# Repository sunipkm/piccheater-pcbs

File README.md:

# PICTURE-C/D Heater Controller PCBs
- `dac-brd`: Raspberry Pi Pico 2 based board with 2x 8 channel DACs supplied by a 2.048V precision reference voltage.
- `amp-mezzanine-v2`: A mezzanine board that supports stacking 4x AMP boards. The mezzanine takes power and control signals and pass them to the AMP boards.
- `amp-brd-v3`: A DC-DC converter board with controllable reference voltage that allows adjusting its output voltage between 0V (1V control) and 25.7V (0V control, V<sub>in</sub> > 25.7V). An on-board INA233 monitors the output voltage and current, and a DS28EA00 1-Wire temperature sensor reports board temperature.
- `amp-brd-v4`: A future, in-development version that integrates monitoring and control features using a USB-PD chip. It would allow all 16 boards on one stack.

This repository is a submodule of [`piccheater`](https://github.com/sunipkm/piccheater).

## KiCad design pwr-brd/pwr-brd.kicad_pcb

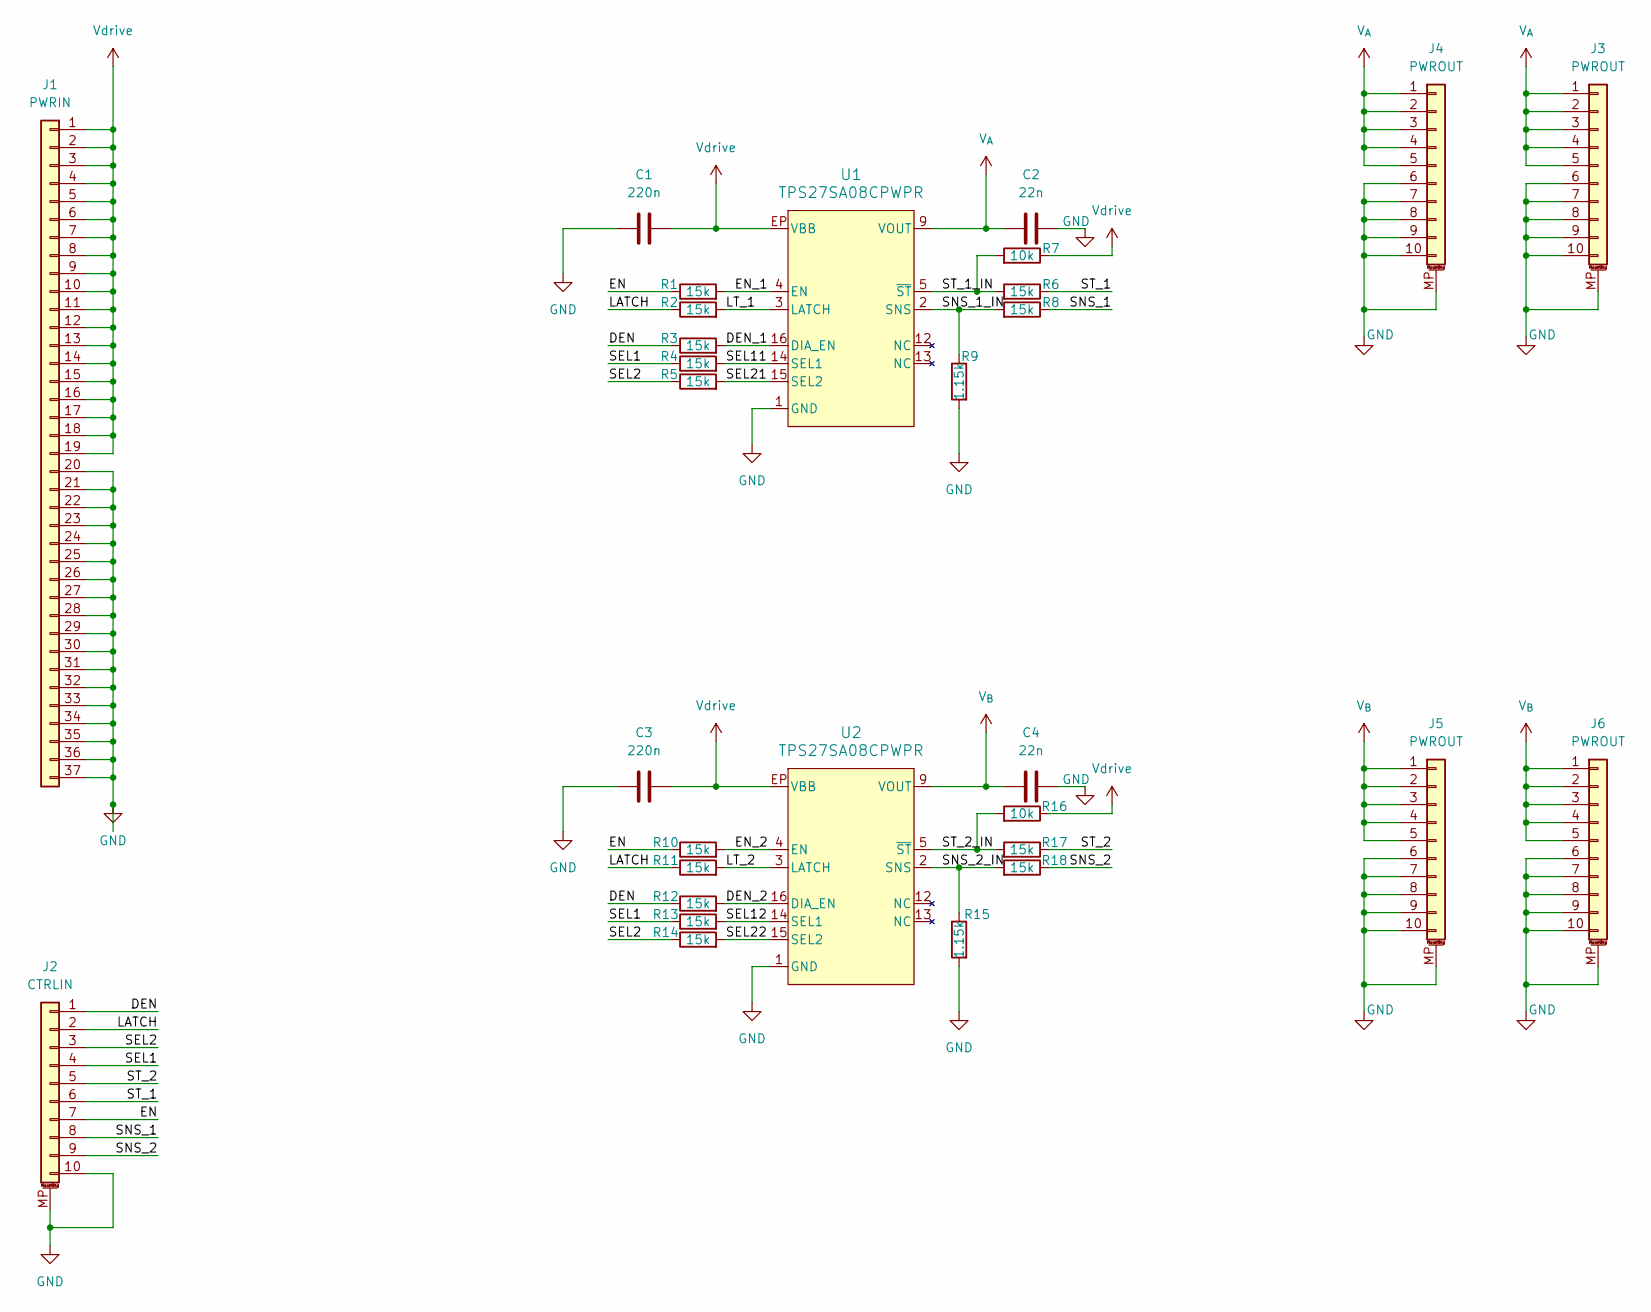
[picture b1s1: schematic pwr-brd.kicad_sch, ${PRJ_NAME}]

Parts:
C1, C3: 220n; C_0603_1608Metric; Mfr # CGA3E3X7R1H224K080AE
C2, C4: 22n; C_0603_1608Metric; Mfr # CGA3E2X8R1H223K080AE
J1: PWRIN; CONN_D37P33E4GX00LF_AMP
J2: CTRLIN; Molex_PicoBlade_53398-1071_1x10-1MP_P1.25mm_Vertical
J3, J4, J5, J6: PWROUT; Molex_PicoBlade_53398-1071_1x10-1MP_P1.25mm_Vertical
R1, R2, R3, R4, R5, R6, R8, R10, R11, R12, R13, R14, R17, R18: 15k; R_0402_1005Metric
R7, R16: 10k; R_0402_1005Metric
R9, R15: 1.15k; R_0402_1005Metric
U1, U2: TPS27SA08CPWPR; TSSOP_CPWPR_TEX; Mfr # TPS27SA08CPWPR

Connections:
/DEN: J2.1, R3.1, R12.1
/DEN_1: R3.2, U1.16 (DIA_EN)
/DEN_2: R12.2, U2.16 (DIA_EN)
/EN: J2.7, R1.1, R10.1
/EN_1: R1.2, U1.4 (EN)
/EN_2: R10.2, U2.4 (EN)
/LATCH: J2.2, R2.1, R11.1
/LT_1: R2.2, U1.3 (LATCH)
/LT_2: R11.2, U2.3 (LATCH)
/SEL1: J2.4, R4.1, R13.1
/SEL2: J2.3, R5.1, R14.1
/SEL11: R4.2, U1.14 (SEL1)
/SEL12: R13.2, U2.14 (SEL1)
/SEL21: R5.2, U1.15 (SEL2)
/SEL22: R14.2, U2.15 (SEL2)
/SNS_1: J2.8, R8.1
/SNS_1_IN: R8.2, R9.1, U1.2 (SNS)
/SNS_2: J2.9, R18.1
/SNS_2_IN: R15.1, R18.2, U2.2 (SNS)
/ST_1: J2.6, R6.1
/ST_1_IN: R6.2, R7.2, U1.5 (~ST)
/ST_2: J2.5, R17.1
/ST_2_IN: R16.2, R17.2, U2.5 (~ST)
GND: C1.1, C2.2, C3.1, C4.2, J1.20, J1.21, J1.22, J1.23, J1.24, J1.25, J1.26, J1.27, J1.28, J1.29, J1.30, J1.31, J1.32, J1.33, J1.34, J1.35, J1.36, J1.37, J2.10, J2.MP (MountPin), J3.6, J3.7, J3.8, J3.9, J3.10, J3.MP (MountPin), J4.6, J4.7, J4.8, J4.9, J4.10, J4.MP (MountPin), J5.6, J5.7, J5.8, J5.9, J5.10, J5.MP (MountPin), J6.6, J6.7, J6.8, J6.9, J6.10, J6.MP (MountPin), R9.2, R15.2, U1.1 (GND), U2.1 (GND)
V_{A}: C2.1, J3.1, J3.2, J3.3, J3.4, J3.5, J4.1, J4.2, J4.3, J4.4, J4.5, U1.6 (VOUT), U1.7 (VOUT), U1.8 (VOUT), U1.9 (VOUT), U1.10 (VOUT), U1.11 (VOUT)
V_{B}: C4.1, J5.1, J5.2, J5.3, J5.4, J5.5, J6.1, J6.2, J6.3, J6.4, J6.5, U2.6 (VOUT), U2.7 (VOUT), U2.8 (VOUT), U2.9 (VOUT), U2.10 (VOUT), U2.11 (VOUT)
Vdrive: C1.2, C3.2, J1.1, J1.2, J1.3, J1.4, J1.5, J1.6, J1.7, J1.8, J1.9, J1.10, J1.11, J1.12, J1.13, J1.14, J1.15, J1.16, J1.17, J1.18, J1.19, R7.1, R16.1, U1.EP (VBB), U2.EP (VBB)

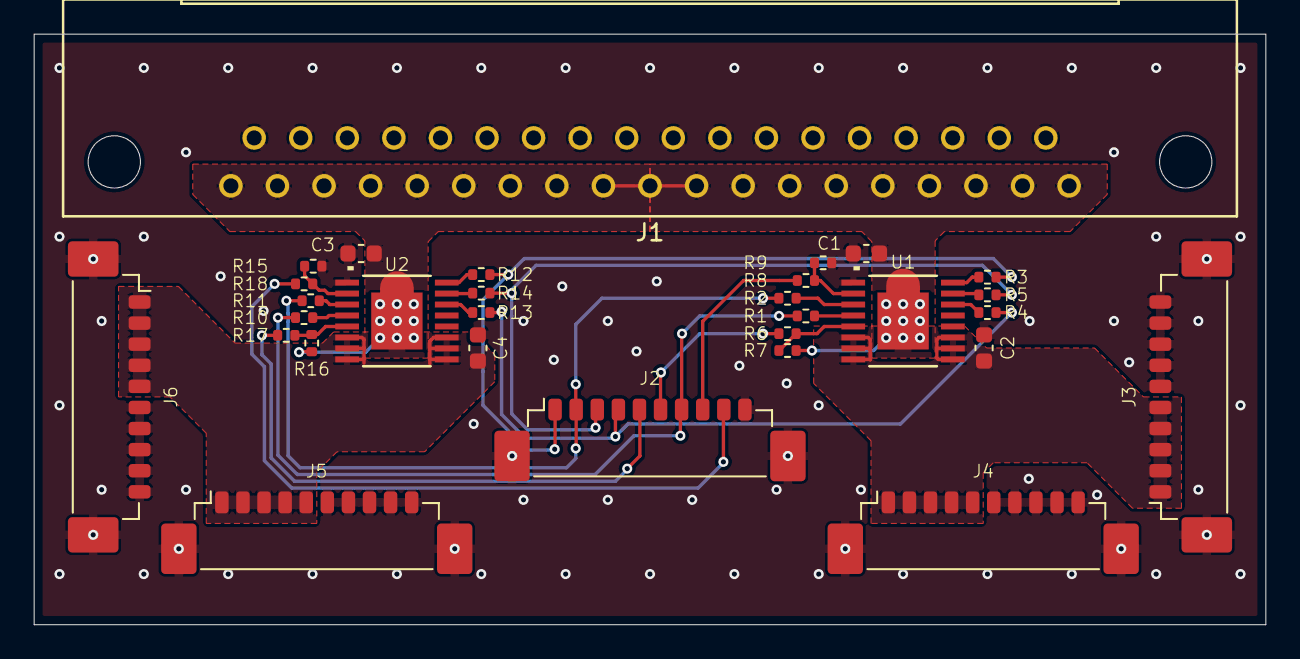
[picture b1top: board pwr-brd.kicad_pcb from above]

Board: 2 copper layers, 73.0 x 35.0 mm, 30 parts (0 on the bottom side), 27 nets.

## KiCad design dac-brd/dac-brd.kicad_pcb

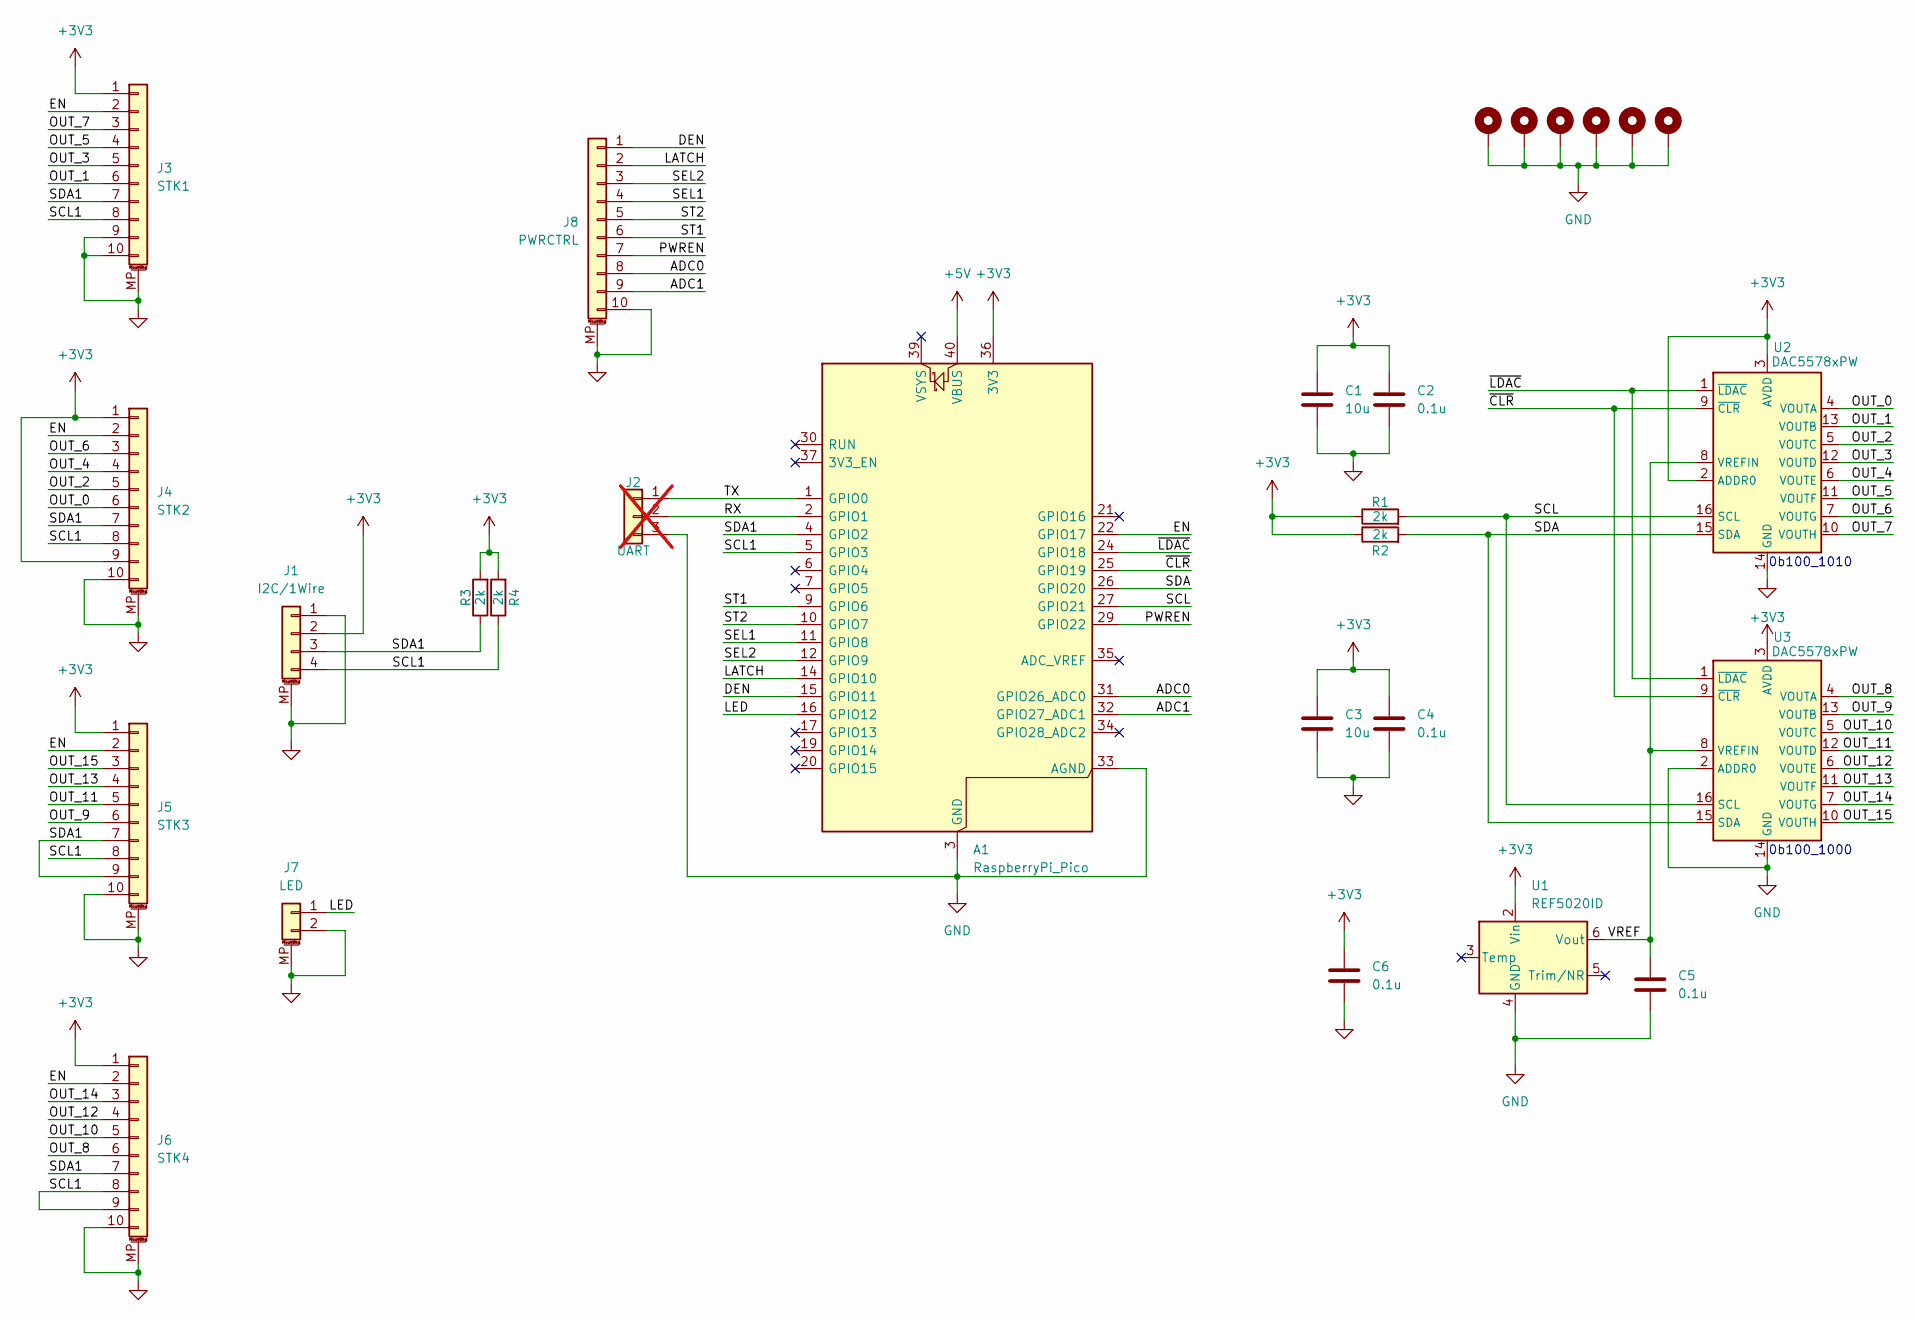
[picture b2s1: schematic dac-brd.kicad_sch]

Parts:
A1: RaspberryPi_Pico; RaspberryPi_Pico_Common_Unspecified
C1, C3: 10u; C_1210_3225Metric
C2, C4, C5, C6: 0.1u; C_0805_2012Metric
H1, H2, H3, H4, H5, H6: MountingHole_2.7mm_M2.5_Pad_Via
J1: I2C/1Wire; JST_SH_BM04B-SRSS-TB_1x04-1MP_P1.00mm_Vertical
J2: UART; PinHeader_1x03_P2.54mm_Vertical; not fitted
J3: STK1; Molex_PicoBlade_53398-1071_1x10-1MP_P1.25mm_Vertical
J4: STK2; Molex_PicoBlade_53398-1071_1x10-1MP_P1.25mm_Vertical
J5: STK3; Molex_PicoBlade_53398-1071_1x10-1MP_P1.25mm_Vertical
J6: STK4; Molex_PicoBlade_53398-1071_1x10-1MP_P1.25mm_Vertical
J7: LED; Molex_PicoBlade_53398-0271_1x02-1MP_P1.25mm_Vertical
J8: PWRCTRL; Molex_PicoBlade_53261-1071_1x10-1MP_P1.25mm_Horizontal
R1, R2, R3, R4: 2k; R_0805_2012Metric
U1: REF5020ID; SOIC-8_3.9x4.9mm_P1.27mm
U2, U3: DAC5578xPW; TSSOP-16_4.4x5mm_P0.65mm

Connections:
+3V3: A1.36 (3V3), C1.1, C2.1, C3.1, C4.1, C6.1, J1.2, J3.1, J4.1, J4.9, J5.1, J6.1, R1.1, R2.1, R3.2, R4.2, U1.2 (Vin), U2.2 (ADDR0), U2.3 (AVDD), U3.3 (AVDD)
+5V: A1.40 (VBUS)
/ADC0: A1.31 (GPIO26_ADC0), J8.8
/ADC1: A1.32 (GPIO27_ADC1), J8.9
/DEN: A1.15 (GPIO11), J8.1
/EN: A1.22 (GPIO17), J3.2, J4.2, J5.2, J6.2
/LATCH: A1.14 (GPIO10), J8.2
/LED: A1.16 (GPIO12), J7.1
/OUT_0: J4.6, U2.4 (VOUTA)
/OUT_1: J3.6, U2.13 (VOUTB)
/OUT_2: J4.5, U2.5 (VOUTC)
/OUT_3: J3.5, U2.12 (VOUTD)
/OUT_4: J4.4, U2.6 (VOUTE)
/OUT_5: J3.4, U2.11 (VOUTF)
/OUT_6: J4.3, U2.7 (VOUTG)
/OUT_7: J3.3, U2.10 (VOUTH)
/OUT_8: J6.6, U3.4 (VOUTA)
/OUT_9: J5.6, U3.13 (VOUTB)
/OUT_10: J6.5, U3.5 (VOUTC)
/OUT_11: J5.5, U3.12 (VOUTD)
/OUT_12: J6.4, U3.6 (VOUTE)
/OUT_13: J5.4, U3.11 (VOUTF)
/OUT_14: J6.3, U3.7 (VOUTG)
/OUT_15: J5.3, U3.10 (VOUTH)
/PWREN: A1.29 (GPIO22), J8.7
/RX: A1.2 (GPIO1), J2.2
/SCL: A1.27 (GPIO21), R1.2, U2.16 (SCL), U3.16 (SCL)
/SCL1: A1.5 (GPIO3), J1.4, J3.8, J4.8, J5.8, J6.8, J6.9, R4.1
/SDA: A1.26 (GPIO20), R2.2, U2.15 (SDA), U3.15 (SDA)
/SDA1: A1.4 (GPIO2), J1.3, J3.7, J4.7, J5.7, J5.9, J6.7, R3.1
/SEL1: A1.11 (GPIO8), J8.4
/SEL2: A1.12 (GPIO9), J8.3
/ST1: A1.9 (GPIO6), J8.6
/ST2: A1.10 (GPIO7), J8.5
/TX: A1.1 (GPIO0), J2.1
/VREF: C5.1, U1.6 (Vout), U2.8 (VREFIN), U3.8 (VREFIN)
/~CLR: A1.25 (GPIO19), U2.9 (~CLR), U3.9 (~CLR)
/~LDAC: A1.24 (GPIO18), U2.1 (~LDAC), U3.1 (~LDAC)
GND: A1.3 (GND), A1.8 (GND), A1.13 (GND), A1.18 (GND), A1.23 (GND), A1.28 (GND), A1.33 (AGND), A1.38 (GND), C1.2, C2.2, C3.2, C4.2, C5.2, C6.2, H1.1, H2.1, H3.1, H4.1, H5.1, H6.1, J1.1, J1.MP (MountPin), J2.3, J3.9, J3.10, J3.MP (MountPin), J4.10, J4.MP (MountPin), J5.10, J5.MP (MountPin), J6.10, J6.MP (MountPin), J7.2, J7.MP (MountPin), J8.10, J8.MP (MountPin), U1.4 (GND), U2.14 (GND), U3.2 (ADDR0), U3.14 (GND)

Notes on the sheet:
0b100_1010
0b100_1000

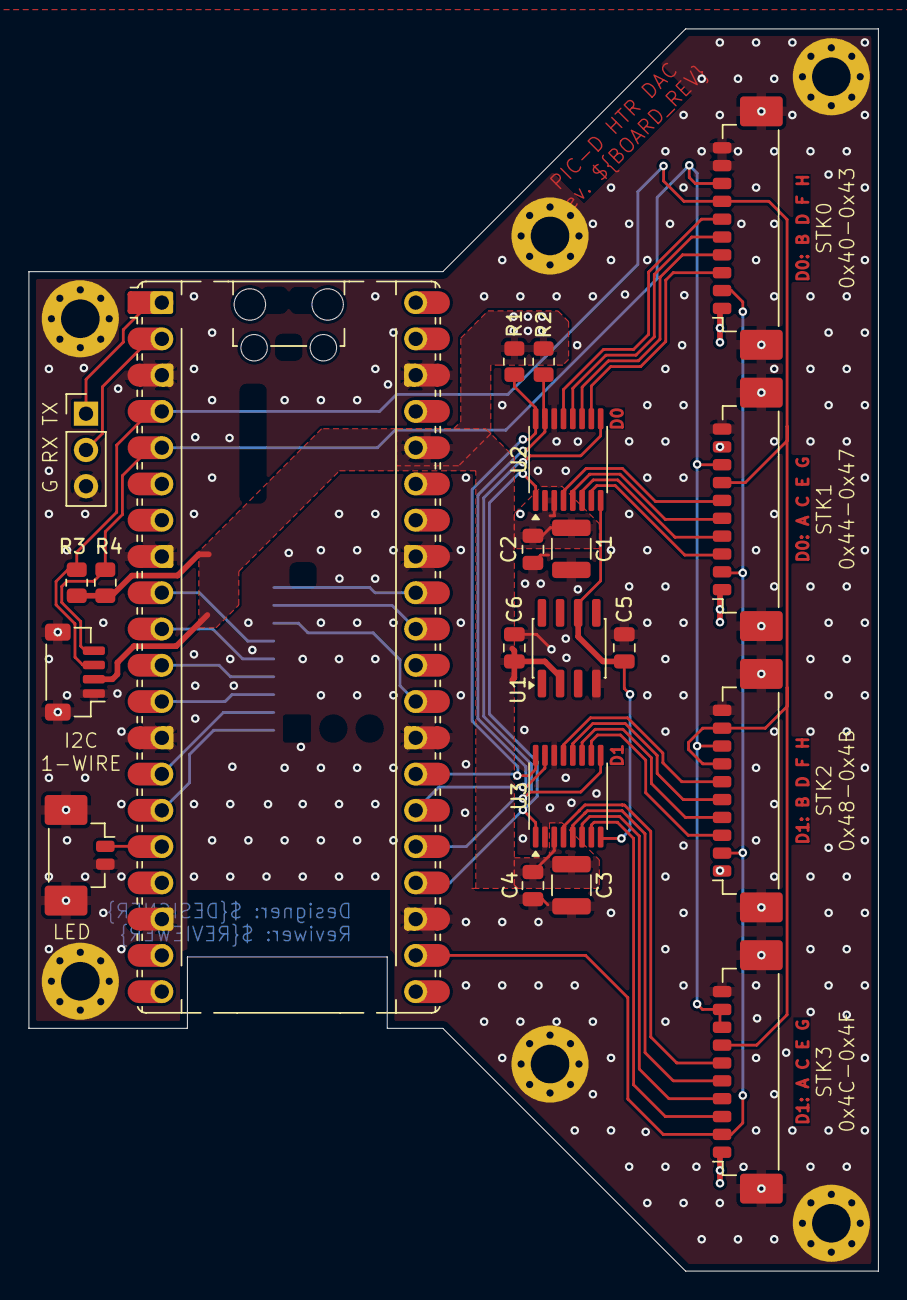
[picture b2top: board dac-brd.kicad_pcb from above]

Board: 4 copper layers, 59.5 x 87.0 mm, 28 parts (1 on the bottom side), 38 nets.

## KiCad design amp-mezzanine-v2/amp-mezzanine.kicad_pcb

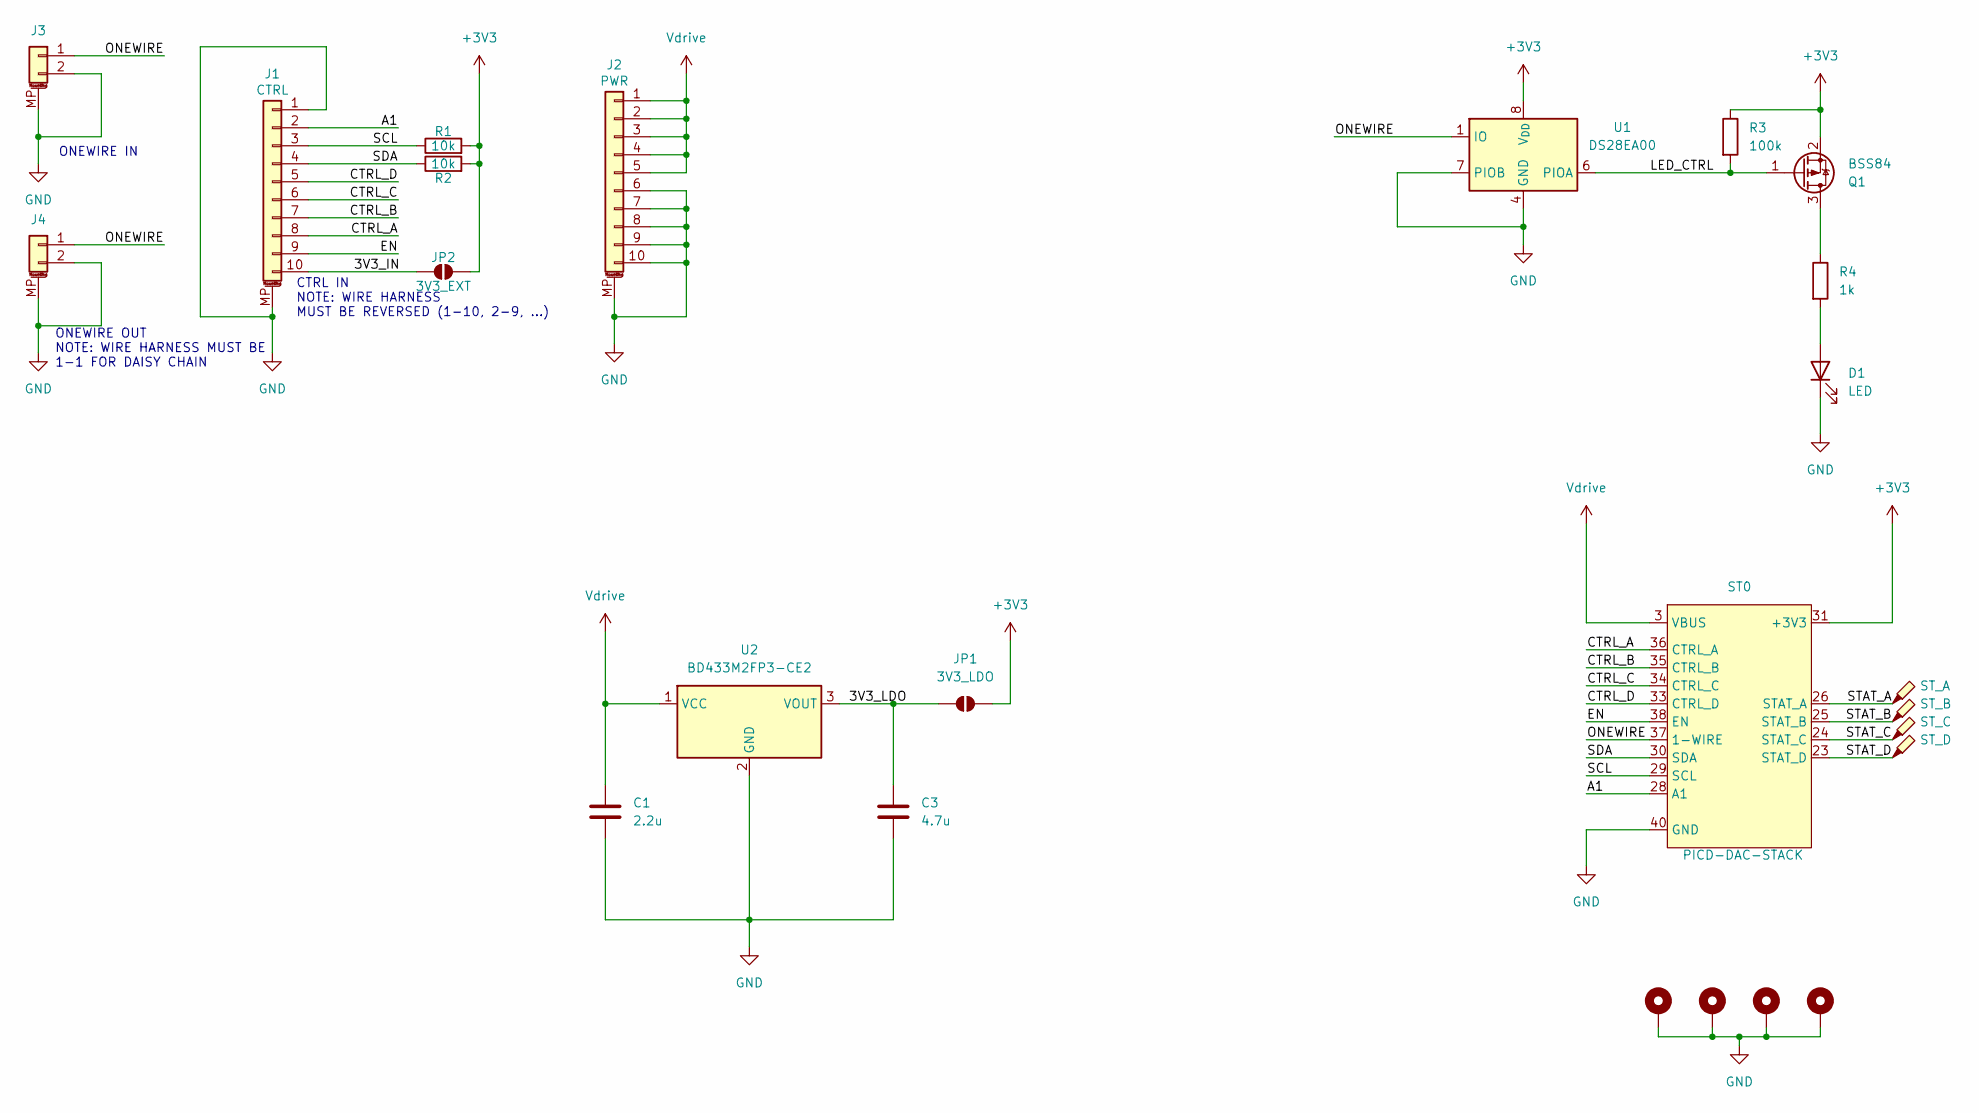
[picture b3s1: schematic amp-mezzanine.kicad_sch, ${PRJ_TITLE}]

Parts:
C1: 2.2u; C_0805_2012Metric; Mfr # CL21Y225KBYVPNE
C3: 4.7u; C_0805_2012Metric; Mfr # MBASE21GBC7475KTCA01
D1: LED; LED_0402_1005Metric; Mfr # 598-2A00-107F
H1, H2, H3, H4: MountingHole_3.2mm_M3_Pad_Via
J1: CTRL; Molex_PicoBlade_53398-1071_1x10-1MP_P1.25mm_Vertical; Mfr # 0533981071
J2: PWR; Molex_PicoBlade_53261-1071_1x10-1MP_P1.25mm_Horizontal; Mfr # 0532611071
J3, J4: ONEWIRE; Molex_PicoBlade_53398-0271_1x02-1MP_P1.25mm_Vertical; Mfr # 0533980271
JP1: 3V3_LDO; SolderJumper-2_P1.3mm_Open_Pad1.0x1.5mm
JP2: 3V3_EXT; SolderJumper-2_P1.3mm_Open_Pad1.0x1.5mm
Q1: BSS84; SOT-23; Mfr # BSS84
R1, R2: 10k; R_0805_2012Metric; Mfr # ERJ-6RBD1002V
R3: 100k; R_0402_1005Metric; Mfr # CRCW0402100KFKED
R4: 1k; R_0402_1005Metric; Mfr # RP73PF1E1K0BTD
ST0: PICD-DAC-STACK; PICCDAC-AMPHENOL-10132797-045100LF; Mfr # 10132797-045100LF
TP1: ST_A; TestPoint_Pad_D1.0mm
TP2: ST_B; TestPoint_Pad_D1.0mm
TP3: ST_C; TestPoint_Pad_D1.0mm
TP4: ST_D; TestPoint_Pad_D1.0mm
U1: DS28EA00; MSOP-8_3x3mm_P0.65mm; Mfr # DS28EA00U+
U2: BD433M2FP3-CE2; SOT230P700X180-4N; Mouser # 755-BD433M2FP3-CE2

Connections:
+3V3: JP1.2 (B), JP2.2 (B), Q1.2 (S), R1.2, R2.2, R3.1, ST0.31 (+3V3), U1.8 (V_{DD})
/3V3_IN: J1.10, JP2.1 (A)
/3V3_LDO: C3.1, JP1.1 (A), U2.3 (VOUT)
/A1: J1.2, ST0.28 (A1)
/CTRL_A: J1.8, ST0.36 (CTRL_A)
/CTRL_B: J1.7, ST0.35 (CTRL_B)
/CTRL_C: J1.6, ST0.34 (CTRL_C)
/CTRL_D: J1.5, ST0.33 (CTRL_D)
/EN: J1.9, ST0.38 (EN)
/LED_CTRL: Q1.1 (G), R3.2, U1.6 (PIOA)
/ONEWIRE: J3.1, J4.1, ST0.37 (1-WIRE), U1.1 (IO)
/SCL: J1.3, R1.1, ST0.29 (SCL)
/SDA: J1.4, R2.1, ST0.30 (SDA)
/STAT_A: ST0.26 (STAT_A), TP1.1
/STAT_B: ST0.25 (STAT_B), TP2.1
/STAT_C: ST0.24 (STAT_C), TP3.1
/STAT_D: ST0.23 (STAT_D), TP4.1
GND: C1.2, C3.2, D1.1 (K), H1.1, H2.1, H3.1, H4.1, J1.1, J1.MP (MountPin), J2.6, J2.7, J2.8, J2.9, J2.10, J2.MP (MountPin), J3.2, J3.MP (MountPin), J4.2, J4.MP (MountPin), ST0.1 (GND), ST0.2 (GND), ST0.19 (GND), ST0.20 (GND), ST0.21 (GND), ST0.22 (GND), ST0.27 (GND), ST0.32 (GND), ST0.39 (GND), ST0.40 (GND), ST0.MP (GND), U1.4 (GND), U1.7 (PIOB), U2.2 (GND), U2.4 (GND)
unnamed: D1.2 (A), R4.2
unnamed: Q1.3 (D), R4.1
Vdrive: C1.1, J2.1, J2.2, J2.3, J2.4, J2.5, ST0.3 (VBUS), ST0.4 (VBUS), ST0.5 (VBUS), ST0.6 (VBUS), ST0.7 (VBUS), ST0.8 (VBUS), ST0.9 (VBUS), ST0.10 (VBUS), ST0.11 (VBUS), ST0.12 (VBUS), ST0.13 (VBUS), ST0.14 (VBUS), ST0.15 (VBUS), ST0.16 (VBUS), ST0.17 (VBUS), ST0.18 (VBUS), U2.1 (VCC)

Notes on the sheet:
ONEWIRE IN
CTRL IN NOTE: WIRE HARNESS MUST BE REVERSED (1-10, 2-9, ...)
ONEWIRE OUT NOTE: WIRE HARNESS MUST BE 1-1 FOR DAISY CHAIN

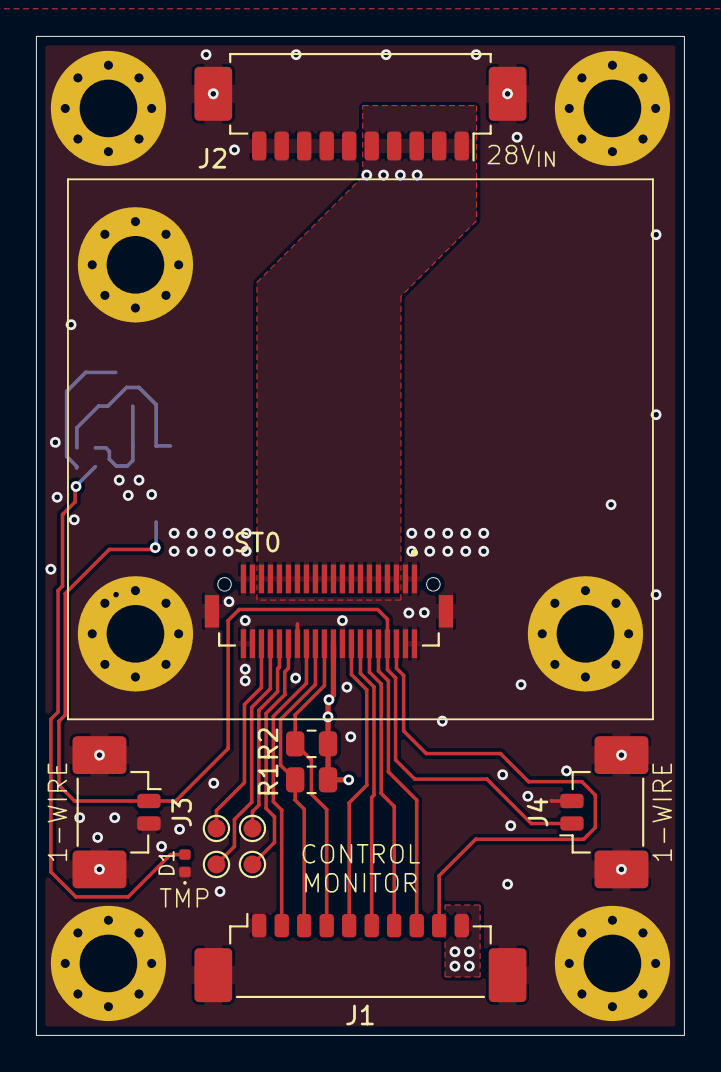
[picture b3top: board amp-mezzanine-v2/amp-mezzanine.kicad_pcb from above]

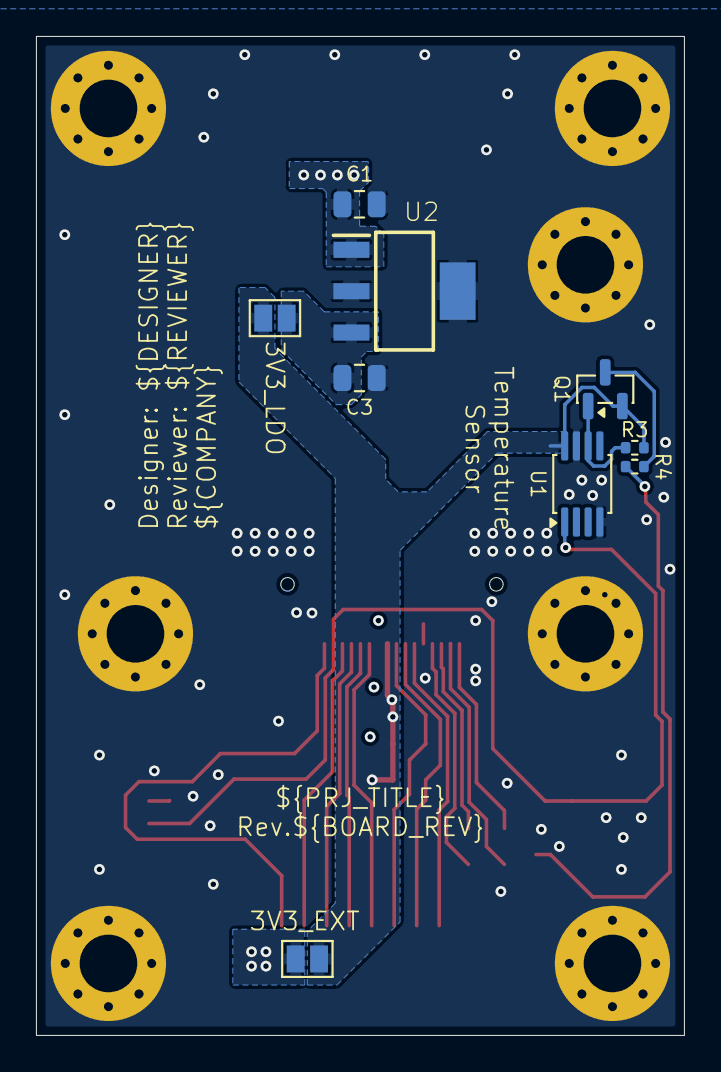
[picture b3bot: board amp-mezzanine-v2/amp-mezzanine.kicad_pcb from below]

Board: 4 copper layers, 36.0 x 55.5 mm, 25 parts (9 on the bottom side), 21 nets.

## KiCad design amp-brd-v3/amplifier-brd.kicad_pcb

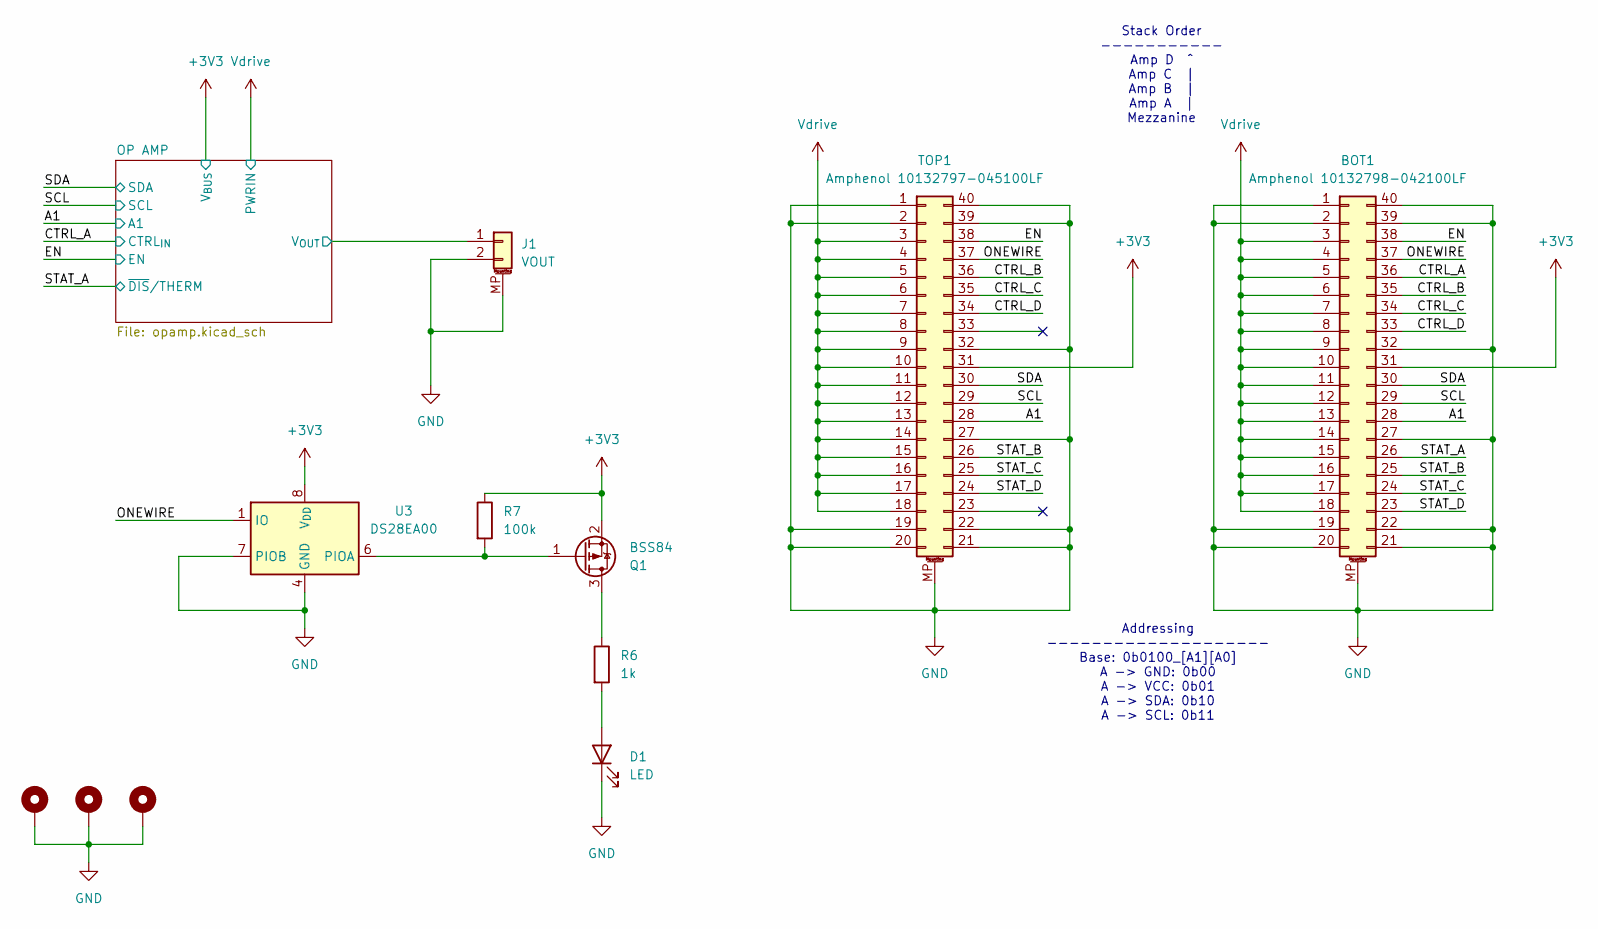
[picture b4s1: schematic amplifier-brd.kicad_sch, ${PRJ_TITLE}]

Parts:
BOT1: Amphenol 10132798-042100LF; AMPHENOL_10132798-042100LF; Mfr # 10132798-042100LF
D1: LED; LED_0402_1005Metric; Mfr # 598-2A00-107F
H1, H2, H4: MountingHole_Pad; MountingHole_3.2mm_M3_Pad_Via
J1: VOUT; Molex_PicoBlade_53261-0271_1x02-1MP_P1.25mm_Horizontal; Mfr # 53261-0271; Mouser # 538-53261-0271
Q1: BSS84; SOT-23; Mfr # BSS84
R6: 1k; R_0402_1005Metric; Mfr # RP73PF1E1K0BTD
R7: 100k; R_0402_1005Metric; Mfr # CRCW0402100KFKED
TOP1: Amphenol 10132797-045100LF; AMPHENOL_10132797-045100LF; Mfr # 10132797-045100LF
U3: DS28EA00; MSOP-8_3x3mm_P0.65mm; Mfr # DS28EA00U+

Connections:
+3V3: BOT1.31, Q1.2 (S), R7.1, TOP1.31, U3.8 (V_{DD}); also elsewhere on the board
/A1: BOT1.28, TOP1.28; also elsewhere on the board
/CTRL_A: BOT1.36; also elsewhere on the board
/CTRL_B: BOT1.35, TOP1.36
/CTRL_C: BOT1.34, TOP1.35
/CTRL_D: BOT1.33, TOP1.34
/EN: BOT1.38, TOP1.38; also elsewhere on the board
/ONEWIRE: BOT1.37, TOP1.37, U3.1 (IO)
/OP AMP/V_{OUT}: J1.1; also elsewhere on the board
/SCL: BOT1.29, TOP1.29; also elsewhere on the board
/SDA: BOT1.30, TOP1.30; also elsewhere on the board
/STAT_A: BOT1.26; also elsewhere on the board
/STAT_B: BOT1.25, TOP1.26
/STAT_C: BOT1.24, TOP1.25
/STAT_D: BOT1.23, TOP1.24
GND: BOT1.1, BOT1.2, BOT1.19, BOT1.20, BOT1.21, BOT1.22, BOT1.27, BOT1.32, BOT1.39, BOT1.40, BOT1.MP (MountPin), D1.1 (K), H1.1, H2.1, H4.1, J1.2, J1.MP (MountPin), TOP1.1, TOP1.2, TOP1.19, TOP1.20, TOP1.21, TOP1.22, TOP1.27, TOP1.32, TOP1.39, TOP1.40, TOP1.MP (MountPin), U3.4 (GND), U3.7 (PIOB); also elsewhere on the board
unnamed: D1.2 (A), R6.2
unnamed: Q1.3 (D), R6.1
unnamed: Q1.1 (G), R7.2, U3.6 (PIOA)
Vdrive: BOT1.3, BOT1.4, BOT1.5, BOT1.6, BOT1.7, BOT1.8, BOT1.9, BOT1.10, BOT1.11, BOT1.12, BOT1.13, BOT1.14, BOT1.15, BOT1.16, BOT1.17, BOT1.18, TOP1.3, TOP1.4, TOP1.5, TOP1.6, TOP1.7, TOP1.8, TOP1.9, TOP1.10, TOP1.11, TOP1.12, TOP1.13, TOP1.14, TOP1.15, TOP1.16, TOP1.17, TOP1.18; also elsewhere on the board

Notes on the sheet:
Stack Order ----------- Amp D ^ Amp C | Amp B | Amp A | Mezzanine
Addressing -------------------- Base: 0b0100_[A1][A0] A -> GND: 0b00 A -> VCC: 0b01 A -> SDA: 0b10 A -> SCL: 0b11

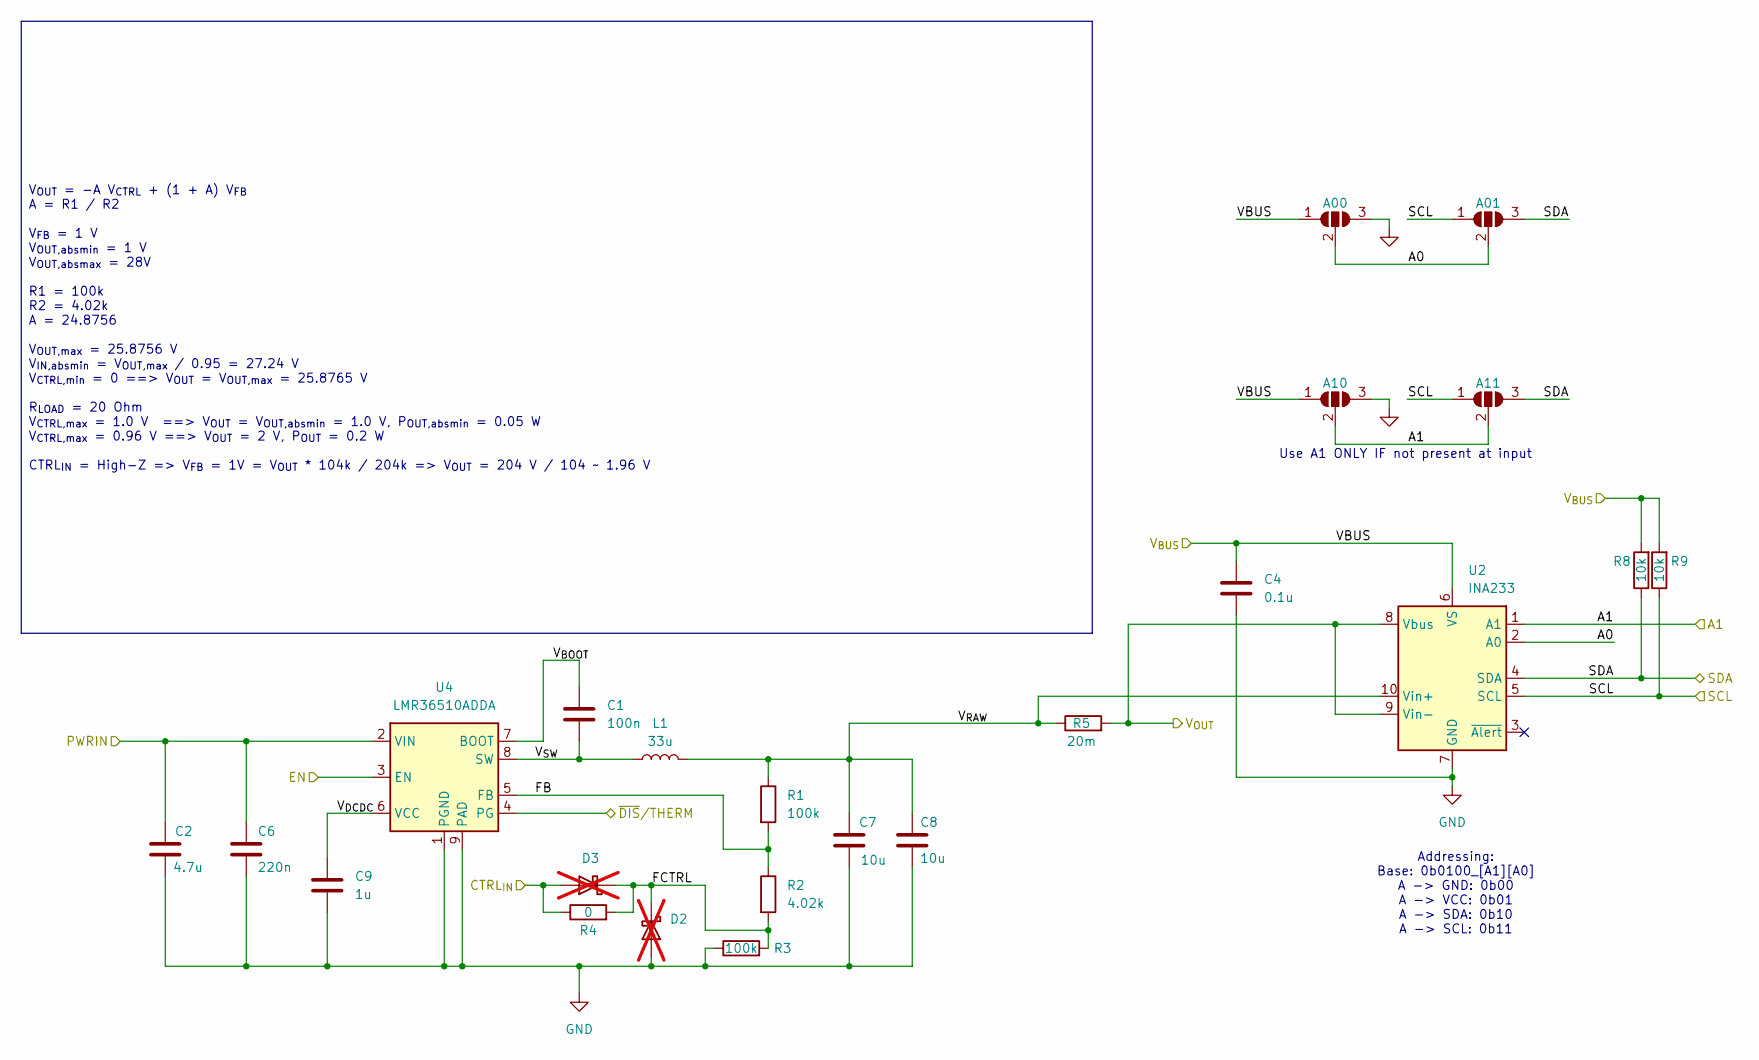
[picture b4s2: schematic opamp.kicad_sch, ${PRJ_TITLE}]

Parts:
A00, A01: L / NC / R; SolderJumper-3_P1.3mm_Open_RoundedPad1.0x1.5mm
A10, A11: NC; SolderJumper-3_P1.3mm_Open_RoundedPad1.0x1.5mm
C1: 100n; C_0402_1005Metric; Mfr # GRM155R71A104KA01D
C2: 4.7u; C_0805_2012Metric; Mfr # MSASU21GBB5475KTNA01
C4: 0.1u; C_0805_2012Metric; Mfr # KAM21BR71H104JM; Mouser # 581-KAM21BR71H104JM
C6: 220n; C_0603_1608Metric; Mfr # C1608X7R1H224K080AB
C7, C8: 10u; C_1210_3225Metric; Mfr # C3225X7R1H106M250AC
C9: 1u; C_0603_1608Metric; Mfr # EMK107B7105KA-T
D2, D3: D_Schottky; D_0402_1005Metric; not fitted
L1: 33u; SDR1105330KL; Mfr # SDR1105-330KL
R1, R3: 100k; R_0402_1005Metric; Mfr # CRCW0402100KFKED
R2: 4.02k; R_0402_1005Metric; Mfr # CRCW04024K02FKED
R4: 0; R_0402_1005Metric; Mfr # MR04X0000FTL
R5: 20m; C_0805_2012Metric; Mfr # RL0805FR-070R02L; Mouser # 603-RL0805FR-070R02L
R8, R9: 10k; R_0402_1005Metric; Mfr # RP73PF1E10KBTD
U2: INA233; VSSOP-10_3x3mm_P0.5mm; Mfr # INA233AIDGSR
U4: LMR36510ADDA; Texas_HTSOP-8-1EP_3.9x4.9mm_P1.27mm_EP2.95x4.9mm_Mask2.4x3.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; Mfr # LMR36510ADDAR

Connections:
+3V3: A00.1 (A), A10.1 (A), C4.1, R8.2, R9.2, U2.6 (VS); also elsewhere on the board
/A1: A10.2 (C), A11.2 (C), U2.1 (A1); also elsewhere on the board
/CTRL_A: D3.2 (A), R4.1; also elsewhere on the board
/EN: U4.3 (EN); also elsewhere on the board
/OP AMP/A0: A00.2 (C), A01.2 (C), U2.2 (A0)
/OP AMP/FB: R1.2, R2.1, U4.5 (FB)
/OP AMP/FCTRL: D2.1 (K), D3.1 (K), R2.2, R3.2, R4.2
/OP AMP/V_{BOOT}: C1.1, U4.7 (BOOT)
/OP AMP/V_{DCDC}: C9.1, U4.6 (VCC)
/OP AMP/V_{OUT}: R5.2, U2.8 (Vbus), U2.9 (Vin-); also elsewhere on the board
/OP AMP/V_{RAW}: C7.1, C8.1, L1.2, R1.1, R5.1, U2.10 (Vin+)
/OP AMP/V_{SW}: C1.2, L1.1, U4.8 (SW)
/SCL: A01.1 (A), A11.1 (A), R9.1, U2.5 (SCL); also elsewhere on the board
/SDA: A01.3 (B), A11.3 (B), R8.1, U2.4 (SDA); also elsewhere on the board
/STAT_A: U4.4 (PG); also elsewhere on the board
GND: A00.3 (B), A10.3 (B), C2.2, C4.2, C6.2, C7.2, C8.2, C9.2, D2.2 (A), R3.1, U2.7 (GND), U4.1 (PGND), U4.9 (PAD); also elsewhere on the board
Vdrive: C2.1, C6.1, U4.2 (VIN); also elsewhere on the board

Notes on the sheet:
Use A1 ONLY IF not present at input
Addressing: Base: 0b0100_[A1][A0] A -> GND: 0b00 A -> VCC: 0b01 A -> SDA: 0b10 A -> SCL: 0b11
V_{OUT} = -A V_{CTRL} + (1 + A) V_{FB} A = R1 / R2 V_{FB} = 1 V V_{OUT,absmin} = 1 V V_{OUT,absmax} = 28V R1 = 100k R2 = 4.02k A = 24.8756 V_{OUT,max} = 25.8756 V V_{IN,absmin} = V_{OUT,max} / 0.95 = 27.24 V V_{CTRL,min} = 0 ==> V_{OUT} = V_{OUT,max} = 25.8765 V R_{LOAD} = 20 Ohm V_{CTRL,max} = 1.0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

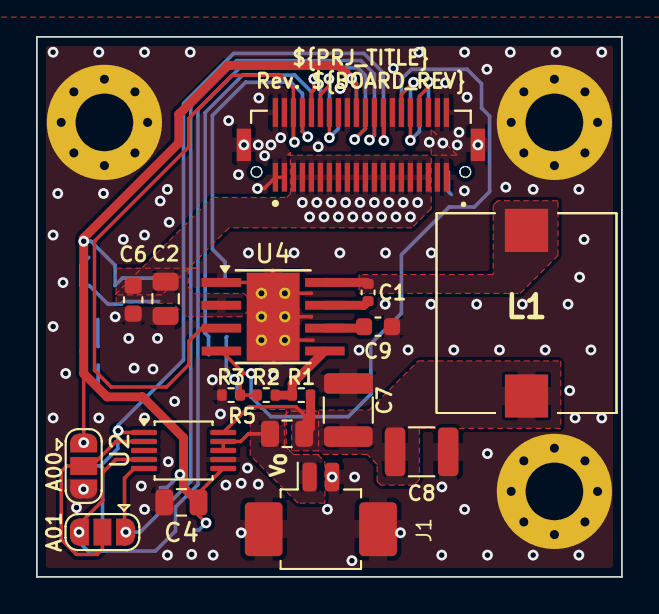
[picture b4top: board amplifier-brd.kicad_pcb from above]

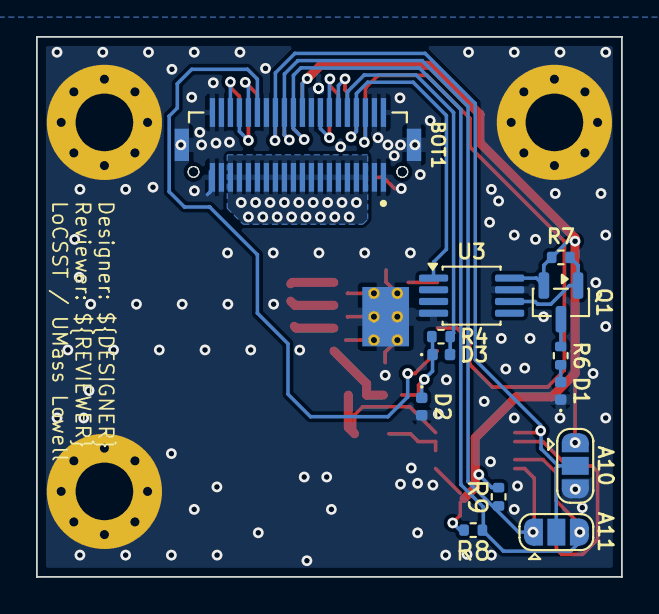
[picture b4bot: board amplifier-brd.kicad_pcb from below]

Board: 4 copper layers, 32.5 x 30.0 mm, 34 parts (13 on the bottom side), 27 nets.
